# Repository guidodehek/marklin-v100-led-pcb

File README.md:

# marklin-v100-led-pcb
LED pcb design for Märklin V100/BR212.

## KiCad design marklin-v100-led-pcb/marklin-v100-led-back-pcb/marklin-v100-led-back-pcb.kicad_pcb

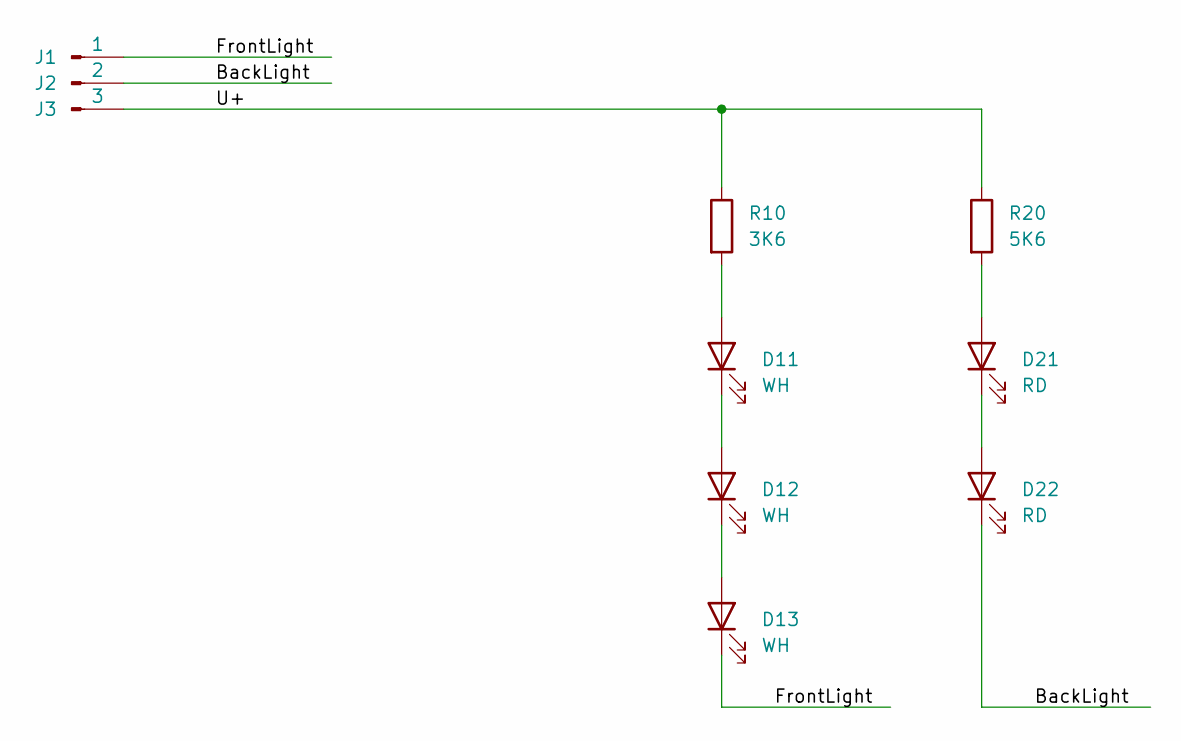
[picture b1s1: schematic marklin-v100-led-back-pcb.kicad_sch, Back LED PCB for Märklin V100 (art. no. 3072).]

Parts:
D11, D12, D13: WH; LED_0603_1608Metric
D21, D22: RD; LED_0603_1608Metric
J1: 1; TestPoint_Pad_2.0x2.0mm
J2: 2; TestPoint_Pad_2.0x2.0mm
J3: 3; TestPoint_Pad_2.0x2.0mm
R10: 3K6; R_0805_2012Metric
R20: 5K6; R_0805_2012Metric

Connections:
/BackLight: D22.1 (K), J2.1
/FrontLight: D13.1 (K), J1.1
/U+: J3.1, R10.1, R20.1
unnamed: D11.1 (K), D12.2 (A)
unnamed: D11.2 (A), R10.2
unnamed: D12.1 (K), D13.2 (A)
unnamed: D21.1 (K), D22.2 (A)
unnamed: D21.2 (A), R20.2

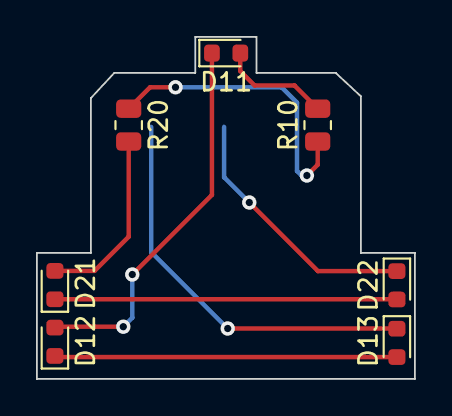
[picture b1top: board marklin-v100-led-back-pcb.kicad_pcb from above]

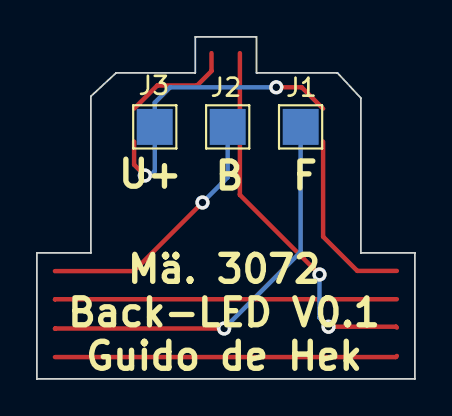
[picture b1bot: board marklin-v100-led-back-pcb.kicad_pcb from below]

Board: 2 copper layers, 21.0 x 19.0 mm, 10 parts (3 on the bottom side), 8 nets.

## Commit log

2021-12-30 feat: add preliminary schematic
2021-12-30 wip: generate netlist and run ERC check
2021-12-30 fix: restore schematic after kicad issue
2021-12-30 feat: first version of layout
2021-12-30 wip: adjust pcb shape
2021-12-31 wip: loco front pcb dimensions
2021-12-31 wip: layout
2021-12-31 wip: cleanup and add project for back pcb
2021-12-31 feat: back pcb layout
2021-12-31 fix: adjust text on front pcb layout
2021-12-31 feat: gerbers for front pcb
2021-12-31 feta: gerbers for back pcb
